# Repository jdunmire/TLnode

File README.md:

Temperature and Light Sensor Node
=================================
This a [KiCad](http://kicad-pcb.org/) design. The node measures
temperature and light levels. It is battery powered and uses the
ESP-8266 module for networking.

Additional information about this node can be found at the 
[Sensor Nodes](http://sensornodeinfo.rockingdlabs.com) website.

Copyright Jerry Dunmire 2015.

This documentation describes Open Hardware and is licensed under the
CERN OHL v. 1.2.

You may redistribute and modify this documentation under the terms of
the CERN OHL v.1.2. (LICENSE.txt). This documentation is distributed
WITHOUT ANY EXPRESS OR IMPLIED WARRANTY, INCLUDING OF MERCHANTABILITY,
SATISFACTORY QUALITY AND FITNESS FOR A PARTICULAR PURPOSE. Please see
the CERN OHL v.1.2 for applicable conditions

Guidelines on how to apply the CERN OHL v1.2 are in the
cern_ohl_v_1_2_howto.pdf file.

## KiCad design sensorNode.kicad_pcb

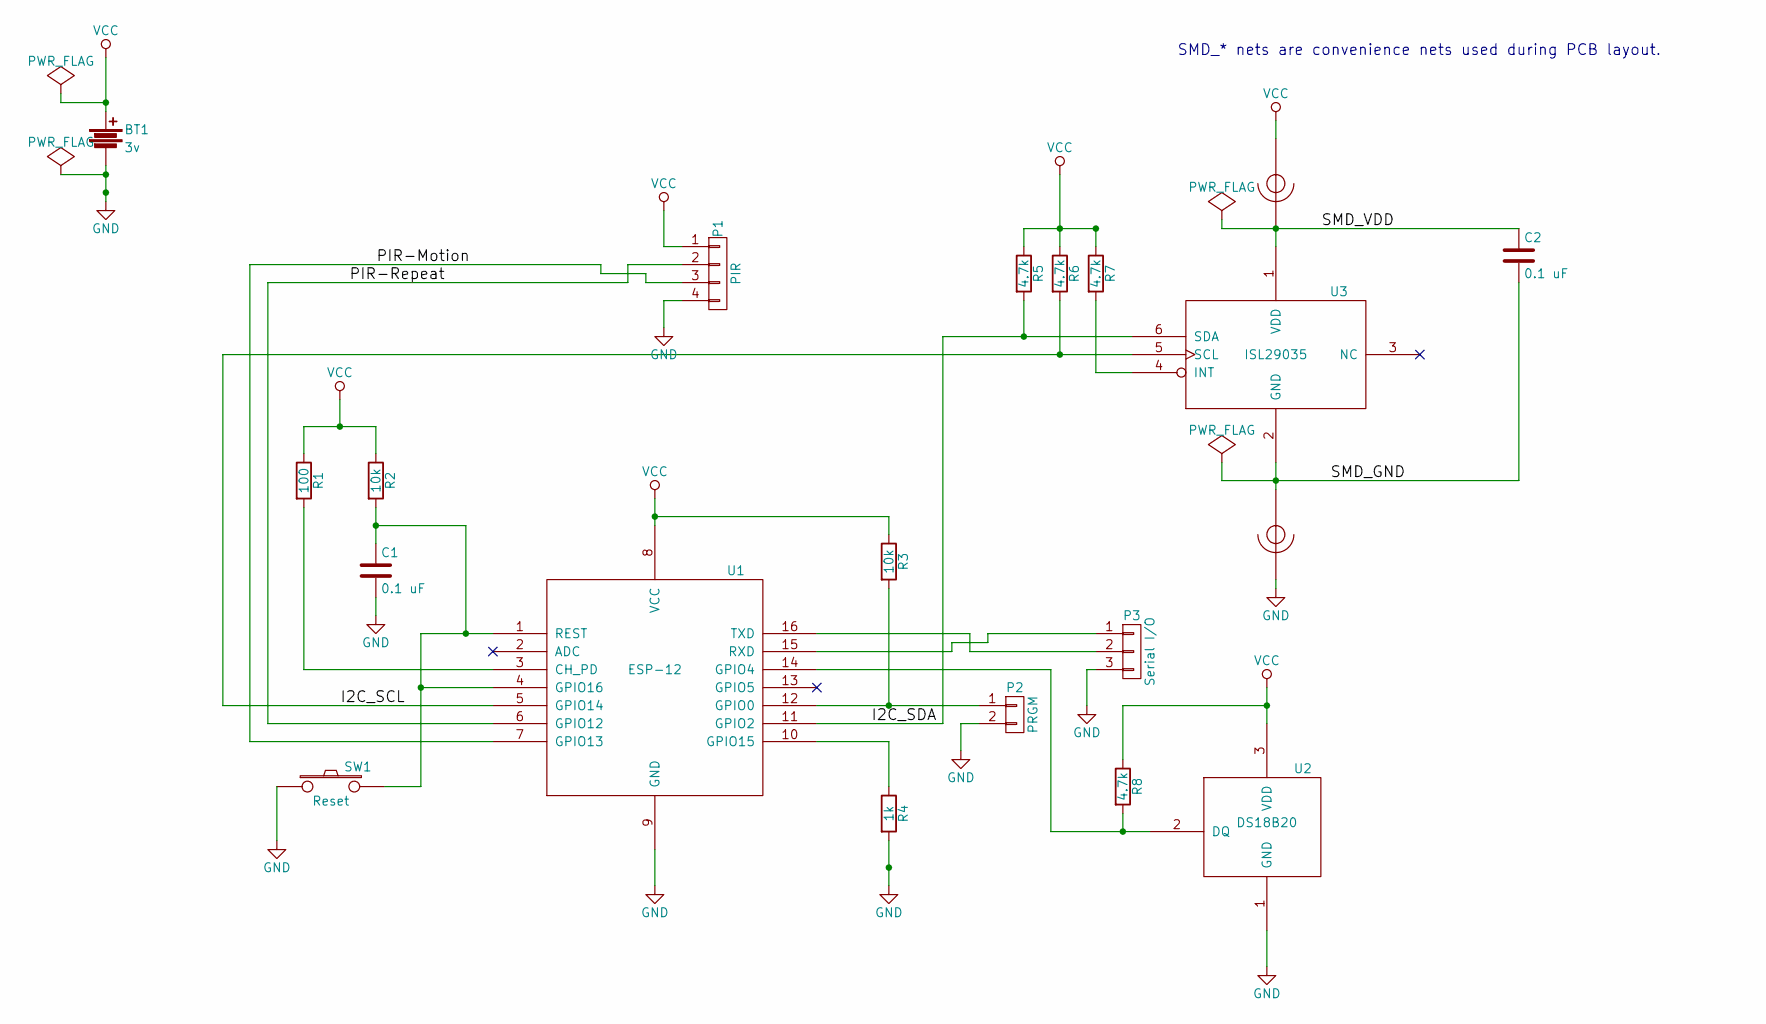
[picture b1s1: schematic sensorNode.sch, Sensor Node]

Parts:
BT1: 3v; BA2AAPC
C1, C2: 0.1 uF; C_0603_HandSoldering
NT1, NT2: Net-Tie-2; NetTie-I_Connected_SMD
P1: PIR; Pin_Header_Angled_1x04
P2: PRGM; Pin_Header_Angled_1x02
P3: Serial I/O; Pin_Header_Angled_1x03
R1: 100; R_0603_HandSoldering
R2, R3: 10k; R_0603_HandSoldering
R4: 1k; R_0603_HandSoldering
R5, R6, R7, R8: 4.7k; R_0603_HandSoldering
SW1: Reset; SW_SPST_E-Switch_TL3302BF180QG
U1: ESP-12
U2: DS18B20; TO-92_Inline_Narrow_Oval
U3: ISL29035; DFN-6_1.5x1.6mm_Pitch0.5mm

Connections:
/I2C_SCL: R6.2, U1.5 (GPIO14), U3.5 (SCL)
/I2C_SDA: R5.2, U1.11 (GPIO2), U3.6 (SDA)
/PIR-Motion: P1.3, U1.7 (GPIO13)
/PIR-Repeat: P1.2, U1.6 (GPIO12)
/SMD_GND: C2.2, NT2.1, U3.2 (GND)
/SMD_VDD: C2.1, NT1.2, U3.1 (VDD)
GND: BT1.2, C1.2, NT2.2, P1.4, P2.2, P3.3, R4.2, SW1.1, U1.9 (GND), U2.1 (GND)
unnamed: C1.1, R2.2, SW1.2, U1.1 (REST), U1.4 (GPIO16)
unnamed: P2.1, R3.2, U1.12 (GPIO0)
unnamed: P3.1, U1.15 (RXD)
unnamed: P3.2, U1.16 (TXD)
unnamed: R1.2, U1.3 (CH_PD)
unnamed: R4.1, U1.10 (GPIO15)
unnamed: R7.2, U3.4 (INT)
unnamed: R8.2, U1.14 (GPIO4), U2.2 (DQ)
VCC: BT1.1, NT1.1, P1.1, R1.1, R2.1, R3.1, R5.1, R6.1, R7.1, R8.1, U1.8 (VCC), U2.3 (VDD)

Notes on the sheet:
SMD_* nets are convenience nets used during PCB layout.

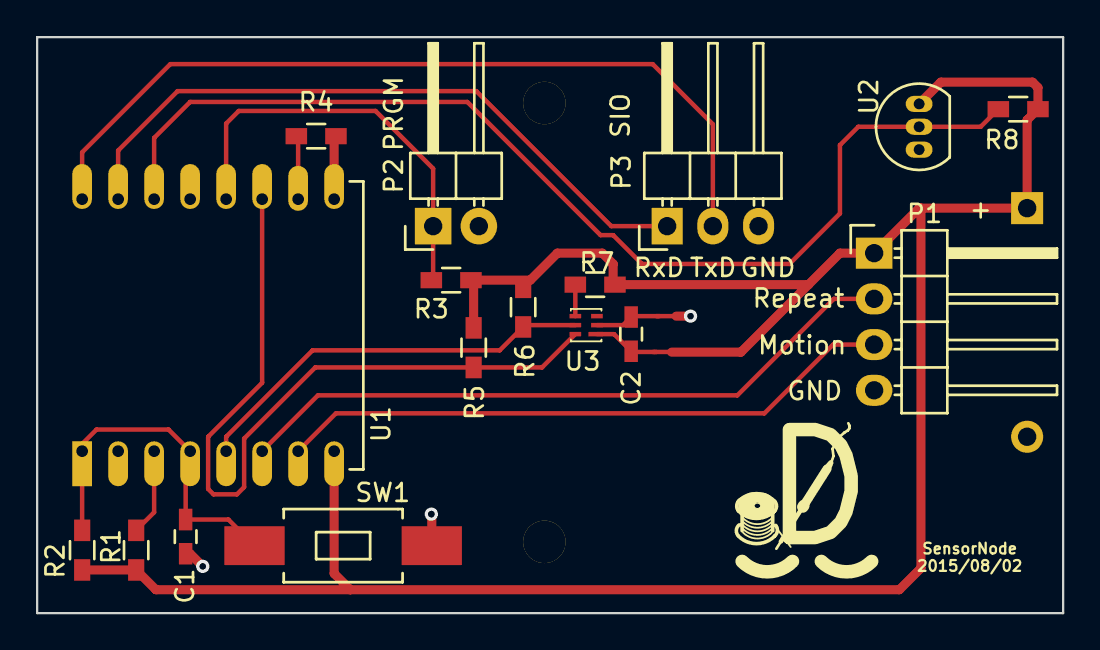
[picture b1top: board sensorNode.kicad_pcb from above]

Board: 2 copper layers, 57.0 x 32.0 mm, 20 parts (1 on the bottom side), 16 nets.

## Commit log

2015-05-21 Initial commit - schematic complete for now
    On branch master
    new file: .gitignore
    new file: CAM/README.md
    new file: rockingdlabs_letter_with_logo.kicad_wks
    new file: sensorNode-cache.lib
    new file: sensorNode.kicad_pcb
2015-05-21 update netlist
    On branch master
    modified: sensorNode.net
2015-05-21 Placed with 1206 parts
    No routing attempted.
    Battery is wrong.
    Board outline is crude approximation of battery holder
    On branch master
    new file: sensorNode.cmp
    modified: sensorNode.kicad_pcb
2015-05-24 Multiple changes
    - Add bypass cap for isl29035
    - Update footprints for battery and isl29035
    - place parts on pcb
    - possibly others
    On branch master
    new file: fp-lib-table
2015-05-24 Route signals and VCC
    Ground plane needs to be added. Two design rule errors for U3 due
    to design rule settings, not real limits.
    A better switch solution would be preferred, having to connect all pins
    and not being able to use common pins as jumpers made routing a lot more
    difficult.
    On branch master
2015-05-24 Add ground plane
    Complete routing. Two design error reported due to default and VCC
    design rule conflict with U3 pad spacing.
    Missing 3d models for switch and ESP8320
    On branch master
    modified: sensorNode.kicad_pcb
2015-05-30 Remove previous PCB files
    On branch newPCB
    deleted: sensorNode.cmp
    deleted: sensorNode.kicad_pcb
    deleted: sensorNode.net
2015-05-30 Add net-tie to divide pwr nets for routing
    On branch newPCB
    modified: sensorNode-cache.lib
    new file: sensorNode.net
    modified: sensorNode.pro
    modified: sensorNode.sch
2015-05-30 Assign packages
    Net-ties and 2-pin button are new.
    On branch newPCB
    new file: sensorNode.cmp
2015-05-31 Check-point: components placed
    Schematic was modified to swap signals on connector pins
    to make routing easier.
    On branch newPCB
    modified: rockingdlabs_letter_with_logo.kicad_wks
    modified: sensorNode.cmp
    new file: sensorNode.kicad_pcb
2015-05-31 Routing complete
    On branch newPCB
    modified: sensorNode.kicad_pcb
2015-07-01 Add labels on silkscreen
    On branch newPCB
    modified: sensorNode.kicad_pcb
2015-08-02 Add script to generate BOM
    On branch newPCB
    new file: bom2csv_tabs.xsl
2015-08-02 Add part details for BOM
    On branch newPCB
    modified: sensorNode.kicad_pcb
    modified: sensorNode.net
    modified: sensorNode.sch
    modified: sensorNode.xml
2015-08-02 Use ESP-12 footprint with smaller silkscreen
    On branch newPCB
    modified: sensorNode.kicad_pcb
2015-08-02 Use batter holder with outline on comments layer
    If outline was left on the silkscreen, the board size would
    have to be larger.
    On branch newPCB
    modified: sensorNode.kicad_pcb
2015-08-02 Rotate logo on bottom
    On branch newPCB
    new file: CAM/.gitignore
    modified: sensorNode.kicad_pcb
2015-11-10 Add version info
    modified: sensorNode.pro
    modified: sensorNode.sch
2015-11-10 Add copyright and license notices
    On branch master
    new file: CHANGES.txt
    new file: LICENSE.txt
    new file: PRODUCT.txt
    new file: README.md
    new file: cern_ohl_v_1_2_howto.pdf
2015-11-10 Fix typos
    On branch master
    modified: README.md

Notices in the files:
sensorNode.kicad_pcb:
Copyright 2015 J. Dunmire
All Rights Reserved
